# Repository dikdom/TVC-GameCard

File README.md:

# TVC-GameCard
Egy IO bővítőkártya a Videoton TV Computerhez, melyen 2 extra joy port és egy SN76489 hangchip található. Ez a kártya a TVC játékos lehetőségeit
bővíti a jobb zenei lehetőségeivel és a 4 játékos üzemmóddal.

Ez a repo a méltán nagysikerű Videoton TV Computerhez készített TVC-GameCard IO kártya leírását és újragyártásához szükséges file-okat tartalmazza.
A kártya 2 extra joy portot, egy SN76489 hangchipet (+3 hangcsatorna +1 zajcsatorna) és 4 extra játékot tartalmaz. Bekapcsoláskor a felhasználó
választhat a játékok közül, de akár tovább is léphet a sima, sztenderd BASIC bekapcsolási képernyőre (...khm... felé, mert ha van több IO kártya
is bedugva a gépbe, akkor simán lehet, hogy a következő kártya fogja megfogni a boot folyamatát..)

Könyvtárstruktúra:
- `doc` dokumentumok a kártyáról
- `src`
  - `menu`
    a boot menü forráskódja, ami az ASM80.com oldalon található IDE-vel készült
  - `gal`
    a GAL20V8B chip kódjainak a forrásai, amit a WinCUPL programmal lehet lefordítani
  - `hw` kapcsolási rajz és board layout EagleCAD formátumban
  - `tvc4snake` a TVC4Snake játék forrása
- `bin`
  minden, ami egy kártya elkészítéséhez szükséges: a gerber file csomagok (TH és SMD konfiguráció, az SMD -hez a gyártási file-ok is a JLC felé), 
  a GAL-ok lefordított .jed file-jai és a EPROM-ba írható bináris, ami a lefordított  boot menüt és a játékokat is tartalmazza

MIT License: minden használható/módosítható, de forrást tessék feltüntetni

An IO expander card for Videoton TV Computer having +2 joy port and an SN76489 sound chip.

MIT License: you can use anything as you want but please, link the source in your project

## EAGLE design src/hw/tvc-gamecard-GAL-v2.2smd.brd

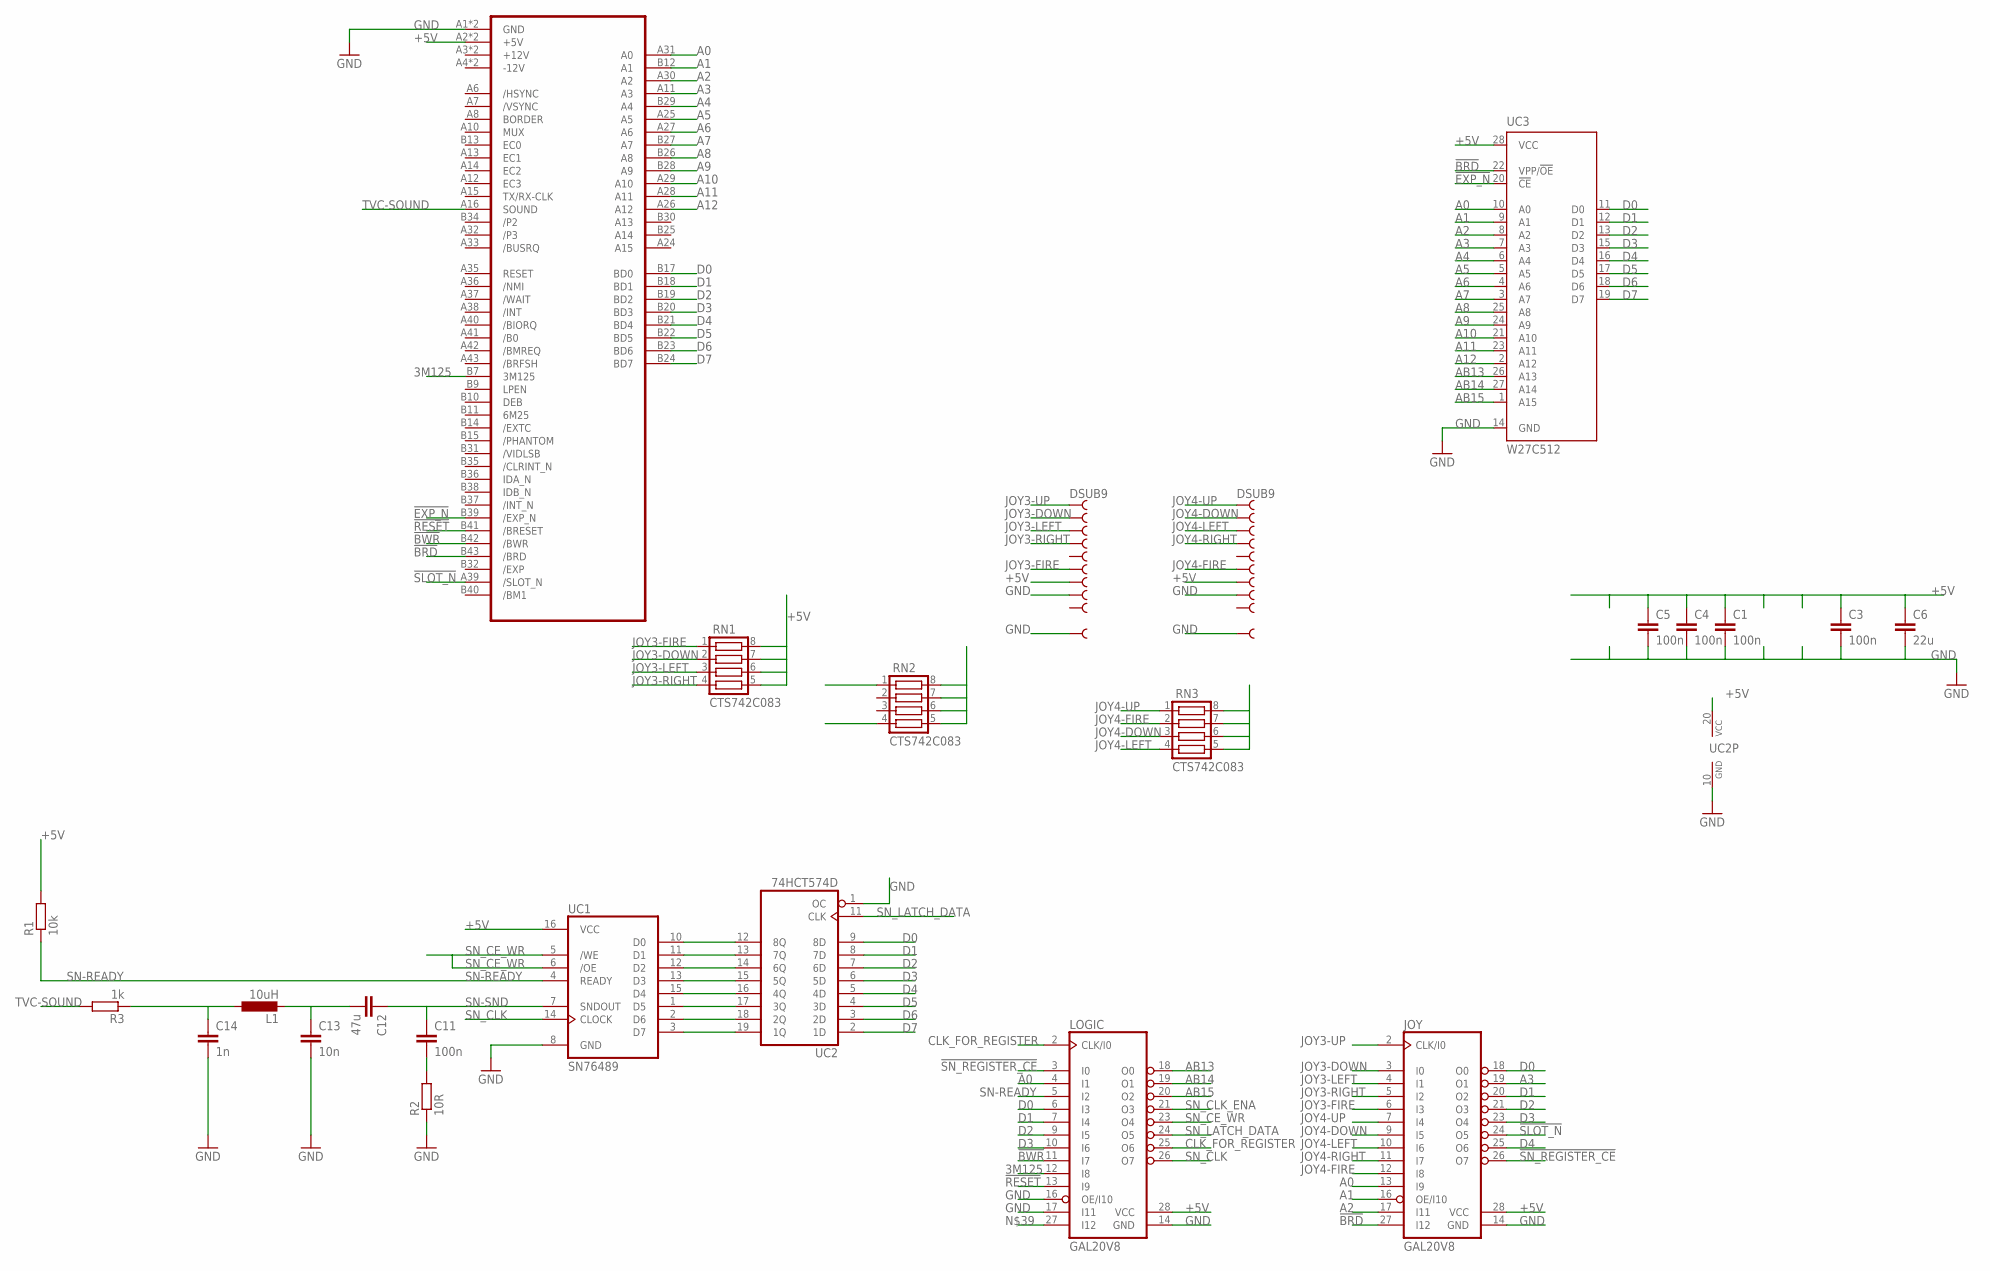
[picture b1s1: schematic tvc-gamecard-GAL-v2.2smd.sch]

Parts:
C1, C3, C4, C5, C11: 100n; C0805
C6: 22u; C0805
C12: 47u; C1206
C13: 10n; C0805
C14: 1n; C0805
CON1: TVC-EXP-HBA-COMMON; TVC-EXP-EDGE
JOY: GAL20V8; PLCC-S28-SOCKET
JOY3, JOY4: DSUB9; H3M09RA
L1: 10uH; L1210
LOGIC: GAL20V8; PLCC-S28-SOCKET
R1: 10k; R0805
R2: 10R; R0805
R3: 1k; R0805
RN1, RN2, RN3: CTS742C083
UC1: SN76489; DIL16
UC2: 74HCT574D; SO20W
UC3: W27C512; DIL28-6

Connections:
3M125: CON1.B7 (3M125), LOGIC.12 (I8)
!BRD: CON1.B43 (/BRD), JOY.27 (I12), UC3.22 (VPP/!OE)
!BWR: CON1.B42 (/BWR), LOGIC.11 (I7)
!EXP_N: CON1.B39 (/EXP_N), UC3.20 (!CE)
!RESET: CON1.B41 (/BRESET), LOGIC.13 (I9)
!SLOT_N: CON1.A39 (/SLOT_N), JOY.24 (O5)
!SN_REGISTER_CE: JOY.26 (O7), LOGIC.3 (I0)
+5V: C1.1, C3.1, C4.1, C5.1, C6.1, CON1.A2 (+5V), CON1.B2 (+5V), JOY.28 (VCC), JOY3.7, JOY4.7, LOGIC.28 (VCC), R1.2, RN1.5, RN1.6, RN1.7, RN1.8, RN2.5, RN2.6, RN2.7, RN2.8, RN3.5, RN3.6, RN3.7, RN3.8, UC1.16 (VCC), UC2.20 (VCC), UC3.28 (VCC)
A0: CON1.A31 (A0), JOY.13 (I9), LOGIC.4 (I1), UC3.10 (A0)
A1: CON1.B12 (A1), JOY.16 (OE/I10), UC3.9 (A1)
A2: CON1.A30 (A2), JOY.17 (I11), UC3.8 (A2)
A3: CON1.A11 (A3), JOY.19 (O1), UC3.7 (A3)
A4: CON1.B29 (A4), UC3.6 (A4)
A5: CON1.A25 (A5), UC3.5 (A5)
A6: CON1.A27 (A6), UC3.4 (A6)
A7: CON1.B27 (A7), UC3.3 (A7)
A8: CON1.B26 (A8), UC3.25 (A8)
A9: CON1.B28 (A9), UC3.24 (A9)
A10: CON1.A29 (A10), UC3.21 (A10)
A11: CON1.A28 (A11), UC3.23 (A11)
A12: CON1.A26 (A12), UC3.2 (A12)
AB13: LOGIC.18 (O0), UC3.26 (A13)
AB14: LOGIC.19 (O1), UC3.27 (A14)
AB15: LOGIC.20 (O2), UC3.1 (A15)
CLK_FOR_REGISTER: LOGIC.2 (CLK/I0), LOGIC.25 (O6)
D0: CON1.B17 (BD0), JOY.18 (O0), LOGIC.6 (I3), UC2.9 (8D), UC3.11 (D0)
D1: CON1.B18 (BD1), JOY.20 (O2), LOGIC.7 (I4), UC2.8 (7D), UC3.12 (D1)
D2: CON1.B19 (BD2), JOY.21 (O3), LOGIC.9 (I5), UC2.7 (6D), UC3.13 (D2)
D3: CON1.B20 (BD3), JOY.23 (O4), LOGIC.10 (I6), UC2.6 (5D), UC3.15 (D3)
D4: CON1.B21 (BD4), JOY.25 (O6), UC2.5 (4D), UC3.16 (D4)
D5: CON1.B22 (BD5), UC2.4 (3D), UC3.17 (D5)
D6: CON1.B23 (BD6), UC2.3 (2D), UC3.18 (D6)
D7: CON1.B24 (BD7), UC2.2 (1D), UC3.19 (D7)
GND: C1.2, C3.2, C4.2, C5.2, C6.2, C13.2, C14.2, CON1.A1 (GND), CON1.B1 (GND), JOY.14 (GND), JOY3.8, JOY3.P$1 (S), JOY3.P$2 (S), JOY4.8, JOY4.P$1 (S), JOY4.P$2 (S), LOGIC.14 (GND), LOGIC.16 (OE/I10), LOGIC.17 (I11), R2.1, UC1.8 (GND), UC2.1 (OC), UC2.10 (GND), UC3.14 (GND)
JOY3-DOWN: JOY.3 (I0), JOY3.2, RN1.2
JOY3-FIRE: JOY.6 (I3), JOY3.6, RN1.1
JOY3-LEFT: JOY.4 (I1), JOY3.3, RN1.3
JOY3-RIGHT: JOY.5 (I2), JOY3.4, RN1.4
JOY3-UP: JOY.2 (CLK/I0), JOY3.1, RN2.4
JOY4-DOWN: JOY.9 (I5), JOY4.2, RN3.3
JOY4-FIRE: JOY.12 (I8), JOY4.6, RN3.2
JOY4-LEFT: JOY.10 (I6), JOY4.3, RN3.4
JOY4-RIGHT: JOY.11 (I7), JOY4.4, RN2.1
JOY4-UP: JOY.7 (I4), JOY4.1, RN3.1
unnamed: C11.2, R2.2
unnamed: C12.2, C13.1, L1.2
unnamed: C14.1, L1.1, R3.1
unnamed: UC1.10 (D0), UC2.12 (8Q)
unnamed: UC1.11 (D1), UC2.13 (7Q)
unnamed: UC1.12 (D2), UC2.14 (6Q)
unnamed: UC1.13 (D3), UC2.15 (5Q)
unnamed: UC1.15 (D4), UC2.16 (4Q)
unnamed: UC1.1 (D5), UC2.17 (3Q)
unnamed: UC1.2 (D6), UC2.18 (2Q)
unnamed: UC1.3 (D7), UC2.19 (1Q)
SN-READY: LOGIC.5 (I2), R1.1, UC1.4 (READY)
SN-SND: C11.1, C12.1, UC1.7 (SNDOUT)
SN_CE_WR: LOGIC.23 (O4), UC1.5 (/WE), UC1.6 (/OE)
SN_CLK: LOGIC.26 (O7), UC1.14 (CLOCK)
SN_CLK_ENA: LOGIC.21 (O3)
SN_LATCH_DATA: LOGIC.24 (O5), UC2.11 (CLK)
TVC-SOUND: CON1.A16 (SOUND), R3.2

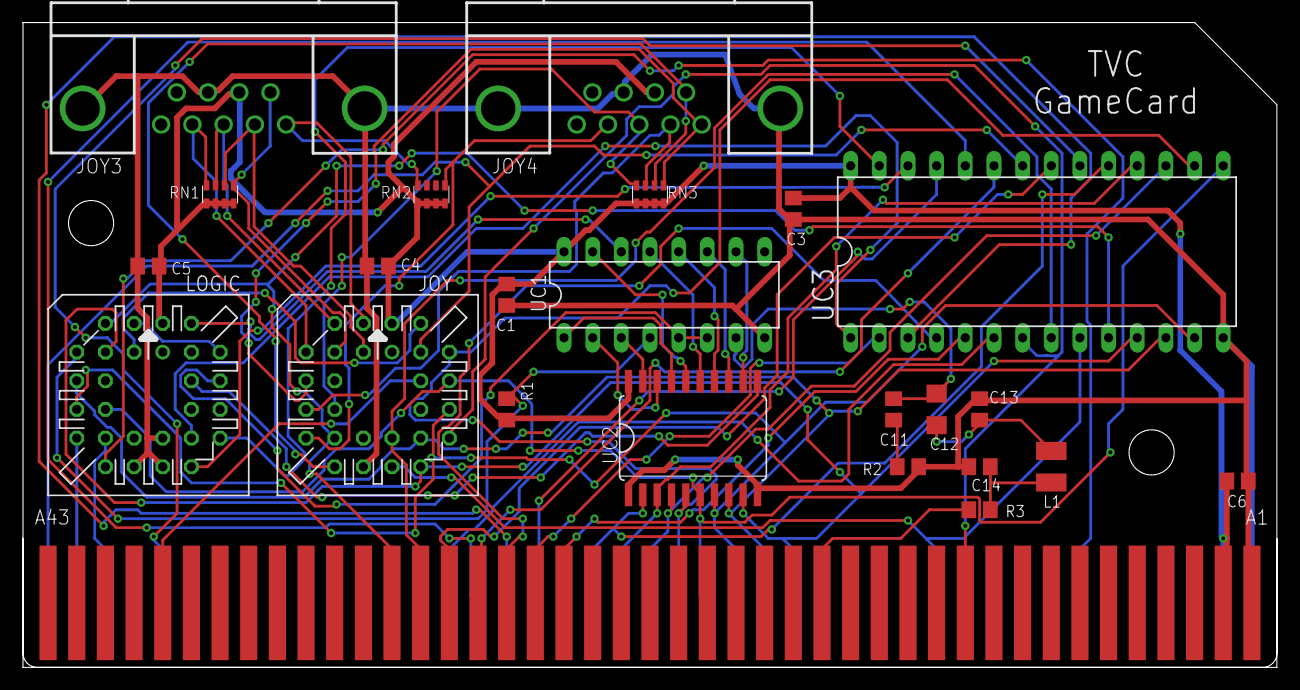
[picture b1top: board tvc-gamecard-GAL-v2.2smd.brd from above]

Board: 2 copper layers, 111.1 x 57.1 mm, 24 parts (0 on the bottom side), 61 nets.

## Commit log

2022-01-05 Update README.md
    Initial README
2022-01-05 initial upload
2022-01-05 C Source of snake game added
2022-01-05 Add files via upload
    typo fixes, comment on SMD cards
